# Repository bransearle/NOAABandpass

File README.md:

# NOAABandpass

A bandpass filter & bias-T powered LNA for receiving APT & LRPT satellite images in the 137MHz region.

The design uses a 3rd-order Butterworth capacitively-coupled LC resonator filter, followed by a Mini-Circuits MMIC preamp.

Supply voltage is 3V-5V to the bias T.

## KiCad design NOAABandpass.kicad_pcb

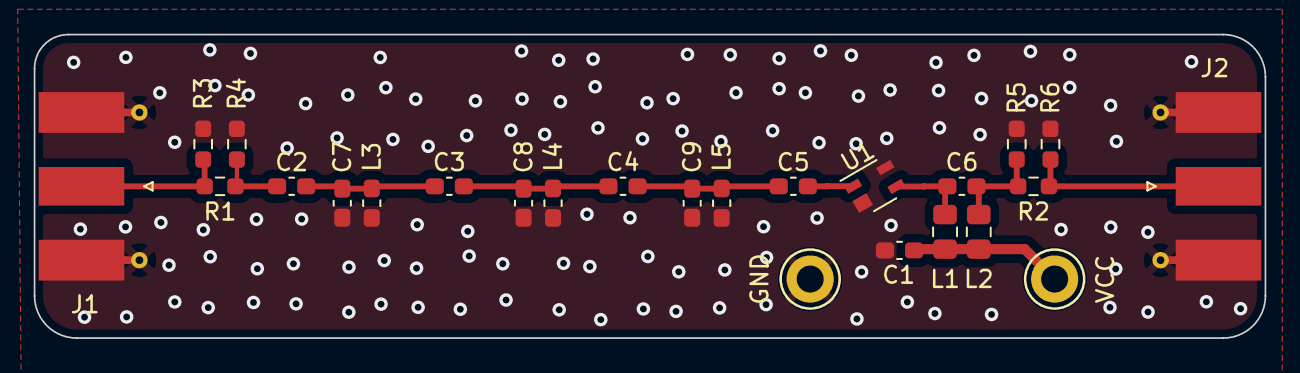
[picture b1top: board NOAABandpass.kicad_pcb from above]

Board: 4 copper layers, 73.0 x 18.0 mm, 25 parts (0 on the bottom side), 11 nets.

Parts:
C1: 100n; C_0603_1608Metric_Pad1.08x0.95mm_HandSolder
C2, C5: 6p2; C_0603_1608Metric_Pad1.08x0.95mm_HandSolder
C3, C4: 1p; C_0603_1608Metric_Pad1.08x0.95mm_HandSolder
C6: 10n; C_0603_1608Metric_Pad1.08x0.95mm_HandSolder
C7, C9: 13p; C_0603_1608Metric_Pad1.08x0.95mm_HandSolder
C8: 18p; C_0603_1608Metric_Pad1.08x0.95mm_HandSolder
J1: ANT; SMA_Molex_73251-1153_EdgeMount_Horizontal
J2: RX; SMA_Molex_73251-1153_EdgeMount_Horizontal
L1, L2: 47u; L_0805_2012Metric_Pad1.15x1.40mm_HandSolder
L3, L4, L5: 68n; L_0603_1608Metric_Pad1.05x0.95mm_HandSolder
R1, R2: 0R; R_0603_1608Metric_Pad0.98x0.95mm_HandSolder
R3, R4, R5, R6: NF; R_0603_1608Metric_Pad0.98x0.95mm_HandSolder
TP1: VCC; TestPoint_Keystone_5005-5009_Compact
TP2: GND; TestPoint_Keystone_5005-5009_Compact
U1: PSA4-5043+; Mini-Circuits_MMM1362

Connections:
/LC1: C2.2, C3.1, C7.2, L3.1
/LC2: C3.2, C4.1, C8.2, L4.1
/LC3: C4.2, C5.1, C9.2, L5.1
/LNA-IN: C5.2, U1.1
/LNA-OUT: C6.1, L1.2, U1.3
/RF-IN: J1.1 (In), R1.1, R3.2
/RF-OUT: J2.1 (In), R2.2, R6.2
/VCC: C1.2, L1.1, L2.1, TP1.1 (TP)
GND: C1.1, C7.1, C8.1, C9.1, J1.2 (Ext), J2.2 (Ext), L3.2, L4.2, L5.2, R3.1, R4.1, R5.1, R6.1, TP2.1 (TP), U1.2 (GND), U1.4 (GND)
unnamed: C2.1, R1.2, R4.2
unnamed: C6.2, L2.2, R2.1, R5.2

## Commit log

2022-11-17 Init from working files
2022-11-17 minor tweak to kibot config
2022-11-17 Adding 4L details to export
2022-11-17 tweaking render colour
2022-11-17 readme details
